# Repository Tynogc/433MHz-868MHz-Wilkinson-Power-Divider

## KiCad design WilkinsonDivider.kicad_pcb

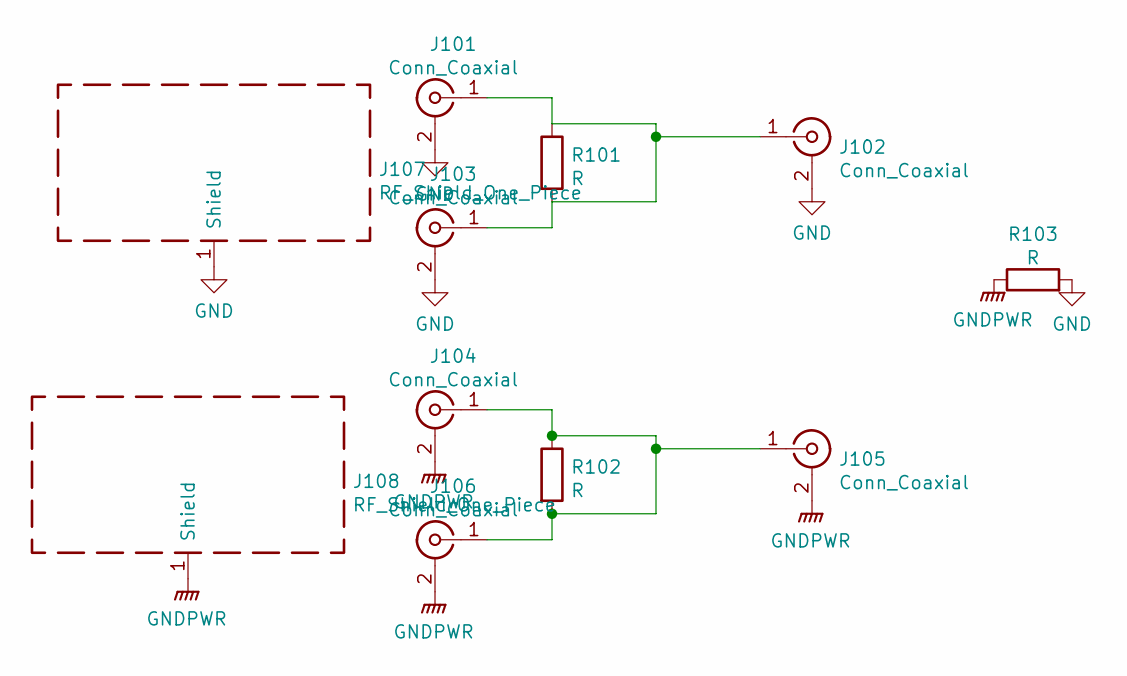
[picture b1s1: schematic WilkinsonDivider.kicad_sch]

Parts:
J101, J102, J103, J104, J105, J106: Conn_Coaxial; SMA_Amphenol_132134-10_Vertical
J107: RF_Shield_One_Piece; Wuerth_36103605_60x60mm
J108: RF_Shield_One_Piece; Wuerth_36103305_30x30mm
R101, R102, R103: R; R_0805_2012Metric

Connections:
GND: J101.2 (Ext), J102.2 (Ext), J103.2 (Ext), J107.1 (Shield), R103.2
GNDPWR: J104.2 (Ext), J105.2 (Ext), J106.2 (Ext), J108.1 (Shield), R103.1
unnamed: J101.1 (In), J102.1 (In), J103.1 (In), R101.1, R101.2
unnamed: J104.1 (In), J105.1 (In), J106.1 (In), R102.1, R102.2

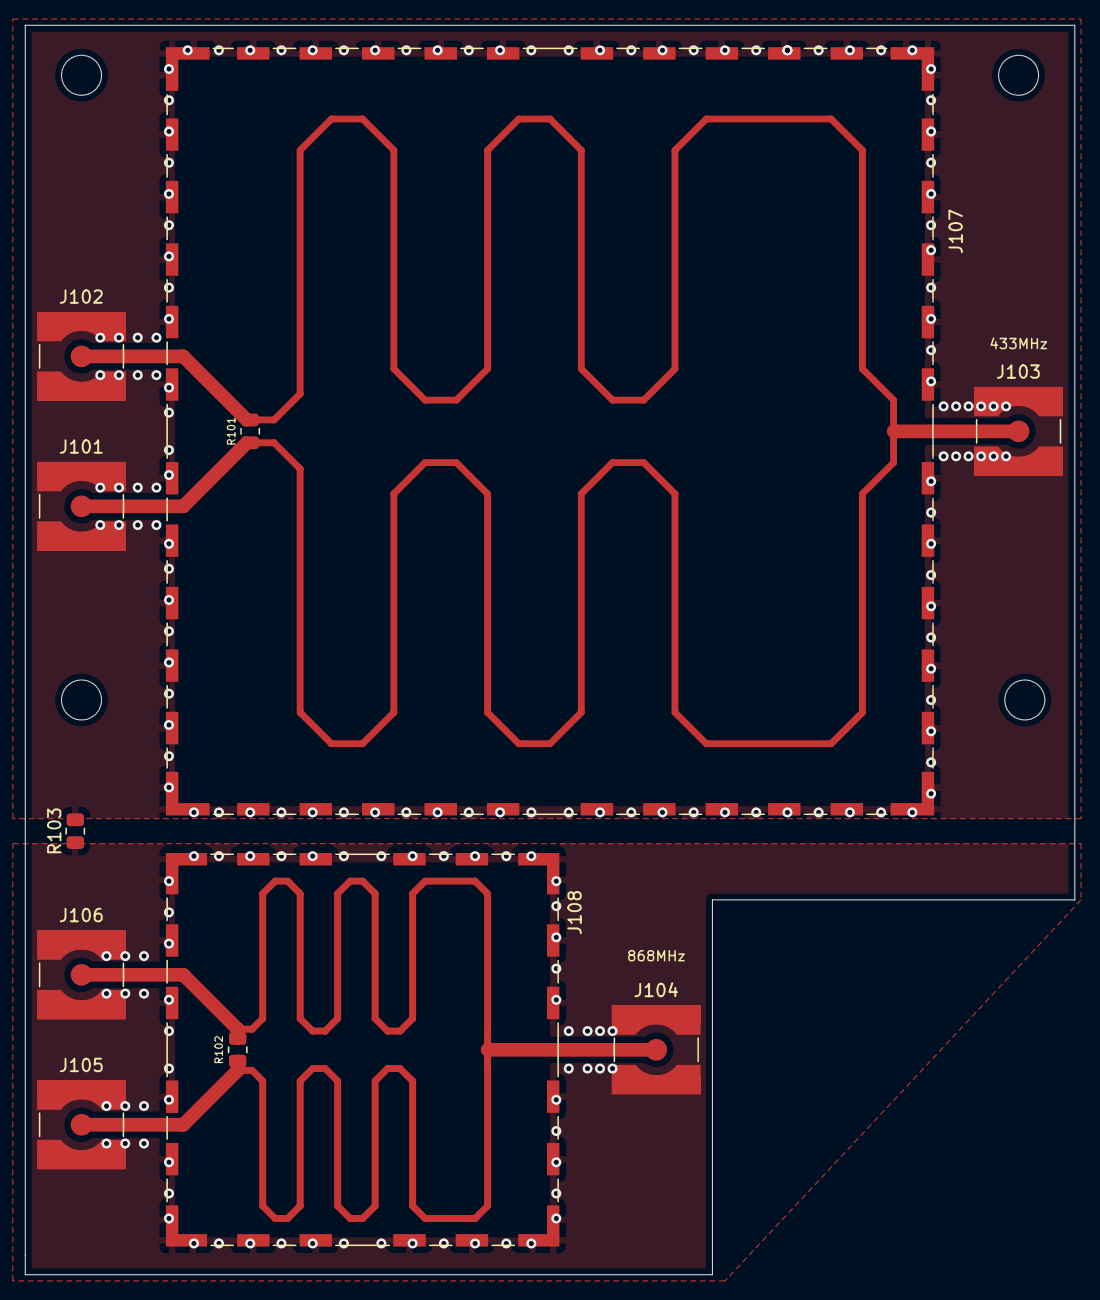
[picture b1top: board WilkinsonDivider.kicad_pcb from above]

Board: 2 copper layers, 84.0 x 100.0 mm, 11 parts (0 on the bottom side), 4 nets.

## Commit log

2021-06-10 Version 0.1 pure PCB without RF-Shielding
